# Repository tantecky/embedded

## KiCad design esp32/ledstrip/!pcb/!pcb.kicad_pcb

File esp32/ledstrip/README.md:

# LEDStrip

A board for controlling a WS2812B LED strip (5V). It contains ESP32 and a digital microphone INMP441.

## Content

- [PCB](!pcb/) design in KiCad
- [src/](src) an example app
- [3D printed enclosure](https://github.com/tantecky/embedded/tree/master/3Dprint/ledstrip) in FreeCAD

## Pics

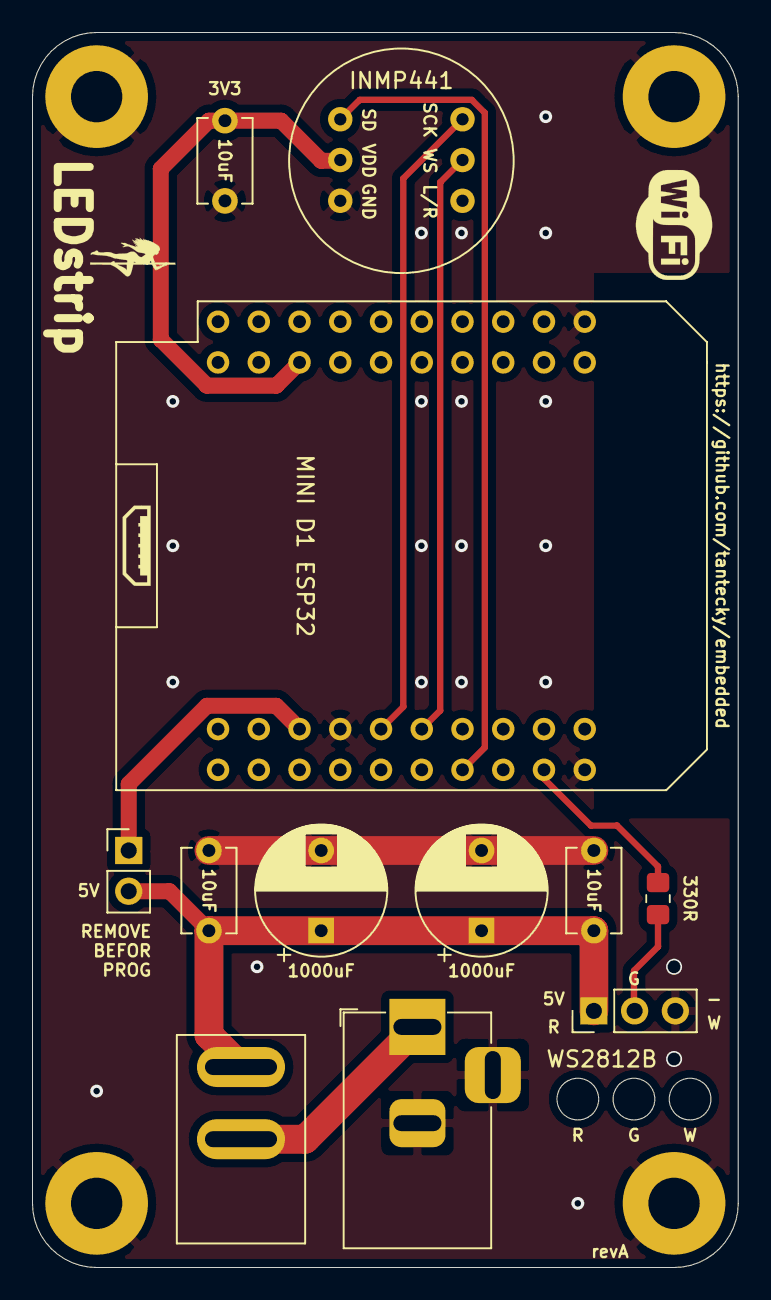
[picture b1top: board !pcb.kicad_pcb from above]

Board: 2 copper layers, 44.0 x 77.0 mm, 16 parts (0 on the bottom side), 10 nets.

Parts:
C1, C2: 1000u; CP_Radial_D8.0mm_P5.00mm
C3, C4, C5: 10u; C_Disc_D5.1mm_W3.2mm_P5.00mm
H1, H2, H3, H4: MountingHole_Pad; MountingHole_3.2mm_M3_Pad
J1: Barrel_Jack_Switch; BarrelJack_Horizontal
J2: Conn_01x03; PinHeader_1x03_P2.54mm_Vertical
JP1: Jumper_NC_Small; PinHeader_1x02_P2.54mm_Vertical
R1: 330R; R_0805_2012Metric_Pad1.20x1.40mm_HandSolder
SW1: SW_SPST; sw
U1: ESP32 MINI; ESP32_mini
U2: INMP441

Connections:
+3V3: C5.1, U1.16, U2.5
+5V: C1.1, C2.1, C3.1, C4.1, J2.1, JP1.2, SW1.2
GND: C1.2, C2.2, C3.2, C4.2, C5.2, H1.1, H2.1, H3.1, H4.1, J1.2, J1.3, J2.3, U1.1, U1.22, U1.33, U2.1, U2.4
unnamed: J1.1, SW1.1
unnamed: J2.2, R1.2
unnamed: JP1.1, U1.35
SCK: U1.31, U2.3
SD: U1.28, U2.6
STRIP: R1.1, U1.24
WS: U1.29, U2.2

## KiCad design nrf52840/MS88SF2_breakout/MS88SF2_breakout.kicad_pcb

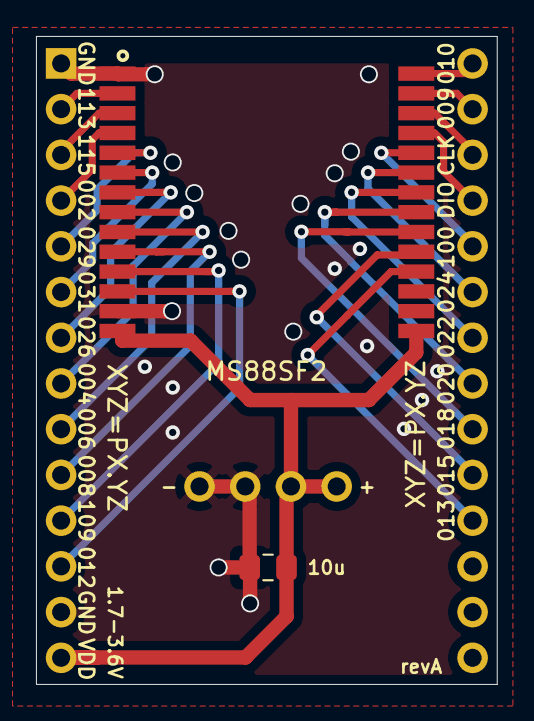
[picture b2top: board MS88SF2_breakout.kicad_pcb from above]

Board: 2 copper layers, 25.6 x 36.0 mm, 5 parts (0 on the bottom side), 24 nets.

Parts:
BT1: Battery_Cell; CR2032_holder
C1: 10uF; C_0805_2012Metric_Pad1.15x1.40mm_HandSolder
J1: Conn_01x14_Male; PinHeader_1x14_P2.54mm_Vertical
J2: Conn_01x14_Male; PinHeader_1x14_P2.54mm_Vertical_2row
U1: MS88SF2

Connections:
+3V3: BT1.1, C1.1, J1.14, U1.14, U1.15
GND: BT1.2, C1.2, J1.1, J1.13, U1.1, U1.13
P0.02: J1.4, U1.4
P0.04: J1.8, U1.8
P0.06: J1.9, U1.9
P0.08: J1.10, U1.10
P0.09: J2.27, U1.27
P0.10: J2.28, U1.28
P0.12: J1.12, U1.12
P0.13: J2.18, U1.18
P0.15: J2.19, U1.19
P0.18: J2.20, U1.20
P0.20: J2.21, U1.21
P0.22: J2.22, U1.22
P0.24: J2.23, U1.23
P0.26: J1.7, U1.7
P0.29: J1.5, U1.5
P0.31: J1.6, U1.6
P1.00: J2.24, U1.24
P1.09: J1.11, U1.11
P1.13: J1.2, U1.2
P1.15: J1.3, U1.3
SWCLK: J2.26, U1.26
SWDIO: J2.25, U1.25

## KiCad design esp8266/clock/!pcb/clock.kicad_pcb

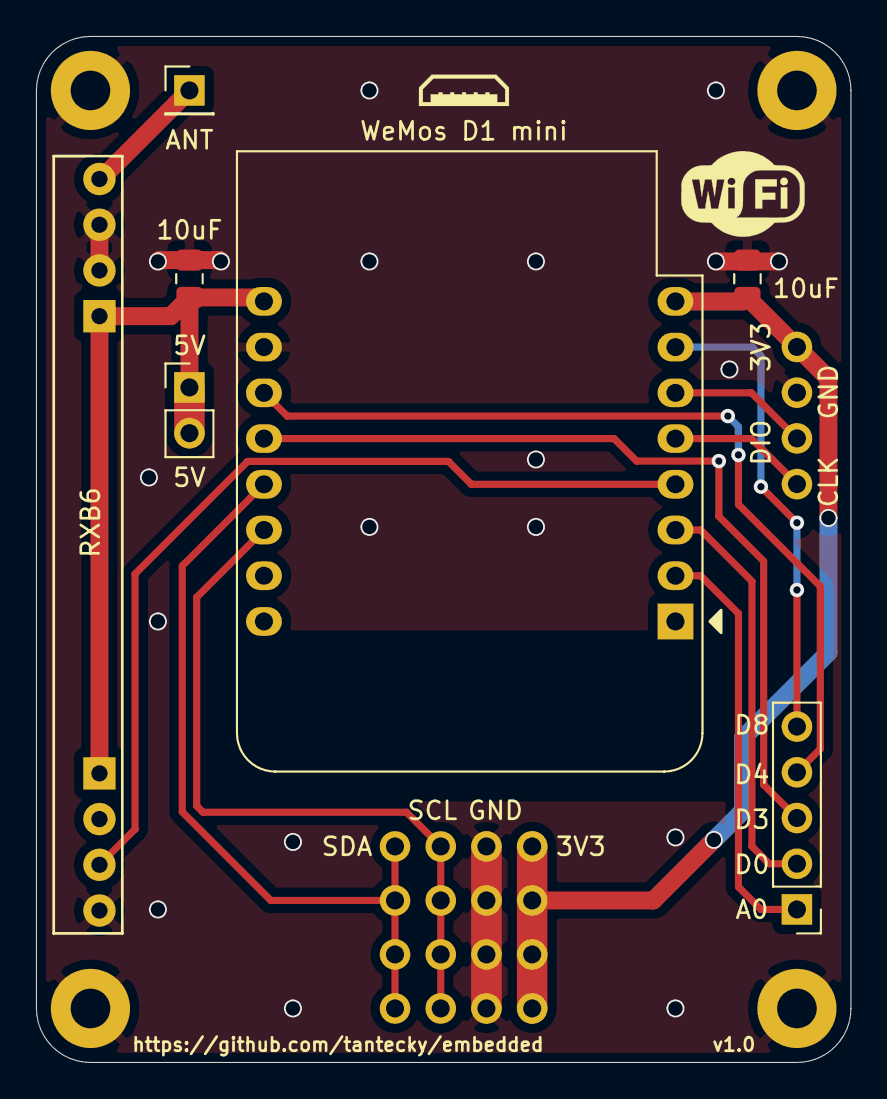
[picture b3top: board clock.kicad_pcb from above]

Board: 2 copper layers, 45.2 x 57.0 mm, 16 parts (0 on the bottom side), 14 nets.

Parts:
5V: Conn_01x01; PinHeader_1x02_P2.54mm_Vertical
10uF, 10uF#2: 10u; C_0805_2012Metric_Pad1.18x1.45mm_HandSolder
ANT: Conn_01x01; PinHeader_1x01_P2.54mm_Vertical
H1, H2, H3, H4: MountingHole_Pad; MountingHole_2.2mm_M2_Pad
J1: GPIO; PinHeader_1x05_P2.54mm_Vertical
RXB6: RXB6; rxb
U3: BME280; 4pinI2C
U4: OLED; 4pinI2C
U5: LED; 4pinTM1637
U6: SPARE; 4pinI2C
U7: SPARE2; 4pinI2C
WeMos D1 mini: WeMos_D1_mini; WEMOS_D1_mini_light

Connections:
+3V3: 10uF#2.2, U3.1, U4.1, U5.1, U6.1, U7.1, WeMos D1 mini.8
+5V: 5V.1, 5V.2, 10uF.1, RXB6.4, RXB6.5, WeMos D1 mini.9
A0: J1.1, WeMos D1 mini.2
ANT: ANT.1, RXB6.8
CLK: U5.4, WeMos D1 mini.5
D0: J1.2, WeMos D1 mini.3
D3: J1.3, WeMos D1 mini.12
D4: J1.4, WeMos D1 mini.11
D8: J1.5, WeMos D1 mini.7
DATA: RXB6.2, WeMos D1 mini.4
DIO: U5.3, WeMos D1 mini.6
GND: 10uF.2, 10uF#2.1, H1.1, H2.1, H3.1, H4.1, RXB6.1, RXB6.6, RXB6.7, U3.2, U4.2, U5.2, U6.2, U7.2, WeMos D1 mini.10
SCL: U3.3, U4.3, U6.3, U7.3, WeMos D1 mini.14
SDA: U3.4, U4.4, U6.4, U7.4, WeMos D1 mini.13

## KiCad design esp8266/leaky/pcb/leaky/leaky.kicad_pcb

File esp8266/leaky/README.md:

# Leaky - water detector
The repository contains a firmware example and KiCad files for open source hardware Leaky. For more info see
<a href="https://www.openhardware.io/view/8239/Leaky-water-detector" target="_blank">project's main page</a> and <a href="https://youtu.be/IXUa7aIcWfs" target="_blank">a short demo.</a>

## Firmware
For an example firmware see [main.cpp](src/main.cpp) and [config.hpp.example](src/config.hpp.example). When a leak is detected it starts beeping, connects to a WiFi and send a MQTT message to a given server.

To program the board an UART dongle is required (e.g. CP2102 USB 2.0 to UART). Is has to support 3V3, do not use 5V!
If you provide power through VBUS, remove batteries first.

To flash a program: 
1. Short jumper PROG
2. Connect UART (RXD->TX, TXD->RX)
3. Short jumper TURN_ON

## Home Assistant integration
Here is an example snippet for `automations.yaml` that forwards a received MQTT message and forwards it to Home Assistant mobile app:
```yaml
- id: 'Leaky'
  alias: Leak
  description: ''
  trigger:
  - platform: mqtt
    topic: leak/#
  condition: []
  action:
  - data_template:
      message: '{{ trigger.payload }}'
    service: notify.mobile_app_mi_a2_lite
  mode: single
  ```

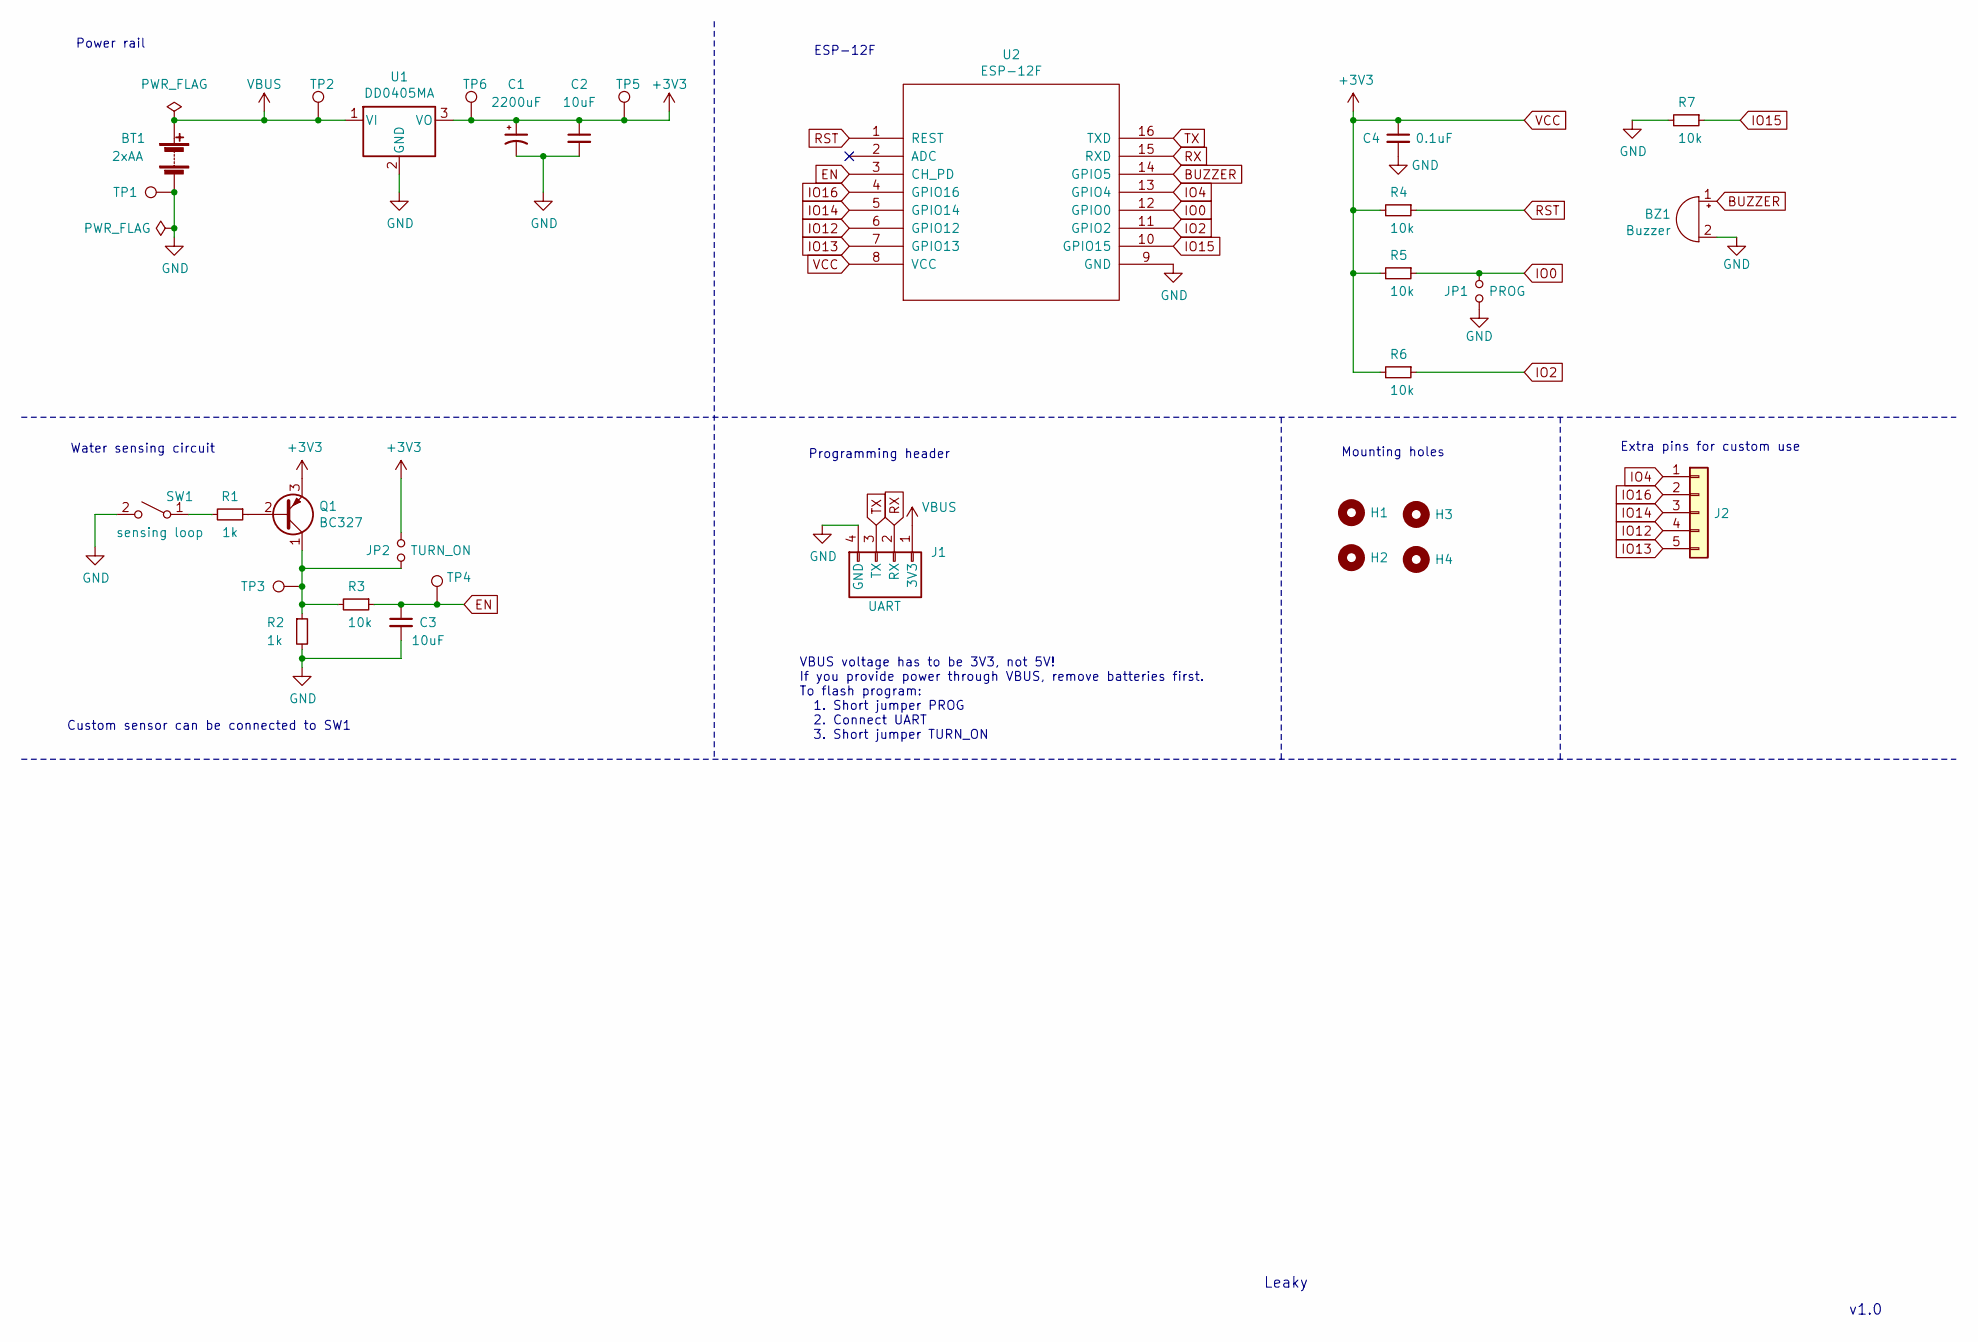
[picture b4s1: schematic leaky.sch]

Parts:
BT1: 2xAA; BatteryHolder_Keystone_2462_2xAA
BZ1: Buzzer; Buzzer_12x9.5RM7.6
C1: 2200uF; CP_Radial_D10.0mm_P5.00mm
C2, C3: 10uF; C_0805_2012Metric_Pad1.18x1.45mm_HandSolder
C4: 0.1uF; C_0805_2012Metric_Pad1.18x1.45mm_HandSolder
H1, H2, H3, H4: MountingHole; MountingHole_3.2mm_M3
J1: UART; PinHeader_1x04_P2.54mm_Vertical
J2: extra pins; PinHeader_1x05_P2.54mm_Vertical
JP1: PROG; PinHeader_1x02_P2.54mm_Vertical
JP2: TURN_ON; PinHeader_1x02_P2.54mm_Vertical
Q1: BC327; TO-92_Inline
R1, R2: 1k; R_0805_2012Metric_Pad1.15x1.40mm_HandSolder
R3, R4, R5, R6, R7: 10k; R_0805_2012Metric_Pad1.15x1.40mm_HandSolder
SW1: sensing loop; PinHeader_1x02_P2.54mm_Vertical
TP1, TP2, TP3, TP4, TP5, TP6: TestPoint; TestPoint_Pad_D1.0mm
U1: DD0405MA
U2: ESP-12F; ESP-12E_SMD

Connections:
BUZZER: BZ1.1 (-), U2.14 (GPIO5)
EN: C3.1, R3.1, TP4.1, U2.3 (CH_PD)
GND: BT1.2 (-), BZ1.2 (+), C1.2, C2.2, C3.2, C4.2, J1.4 (GND), JP1.2, R2.2, R7.2, SW1.2 (B), TP1.1, U1.2 (GND), U2.9 (GND)
IO0: JP1.1, R5.1, U2.12 (GPIO0)
IO2: R6.1, U2.11 (GPIO2)
IO4: J2.1, U2.13 (GPIO4)
IO12: J2.4, U2.6 (GPIO12)
IO13: J2.5, U2.7 (GPIO13)
IO14: J2.3, U2.5 (GPIO14)
IO15: R7.1, U2.10 (GPIO15)
IO16: J2.2, U2.4 (GPIO16)
unnamed: JP2.2, Q1.1 (C), R2.1, R3.2, TP3.1
unnamed: Q1.2 (B), R1.1
unnamed: R1.2, SW1.1 (A)
RST: R4.1, U2.1 (REST)
RX: J1.2 (RX), U2.15 (RXD)
TX: J1.3 (TX), U2.16 (TXD)
VBUS: BT1.1 (+), J1.1 (3V3), TP2.1, U1.1 (VI)
VCC: C1.1, C2.1, C4.1, JP2.1, Q1.3 (E), R4.2, R5.2, R6.2, TP5.1, TP6.1, U1.3 (VO), U2.8 (VCC)

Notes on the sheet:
Power rail
Water sensing circuit
Programming header
Extra pins for custom use
Mounting holes
VBUS voltage has to be 3V3, not 5V! If you provide power through VBUS, remove batteries first. To flash program: 1. Short jumper PROG 2. Connect UART 3. Short jumper TURN_ON
ESP-12F
Custom sensor can be connected to SW1
Leaky
v1.0

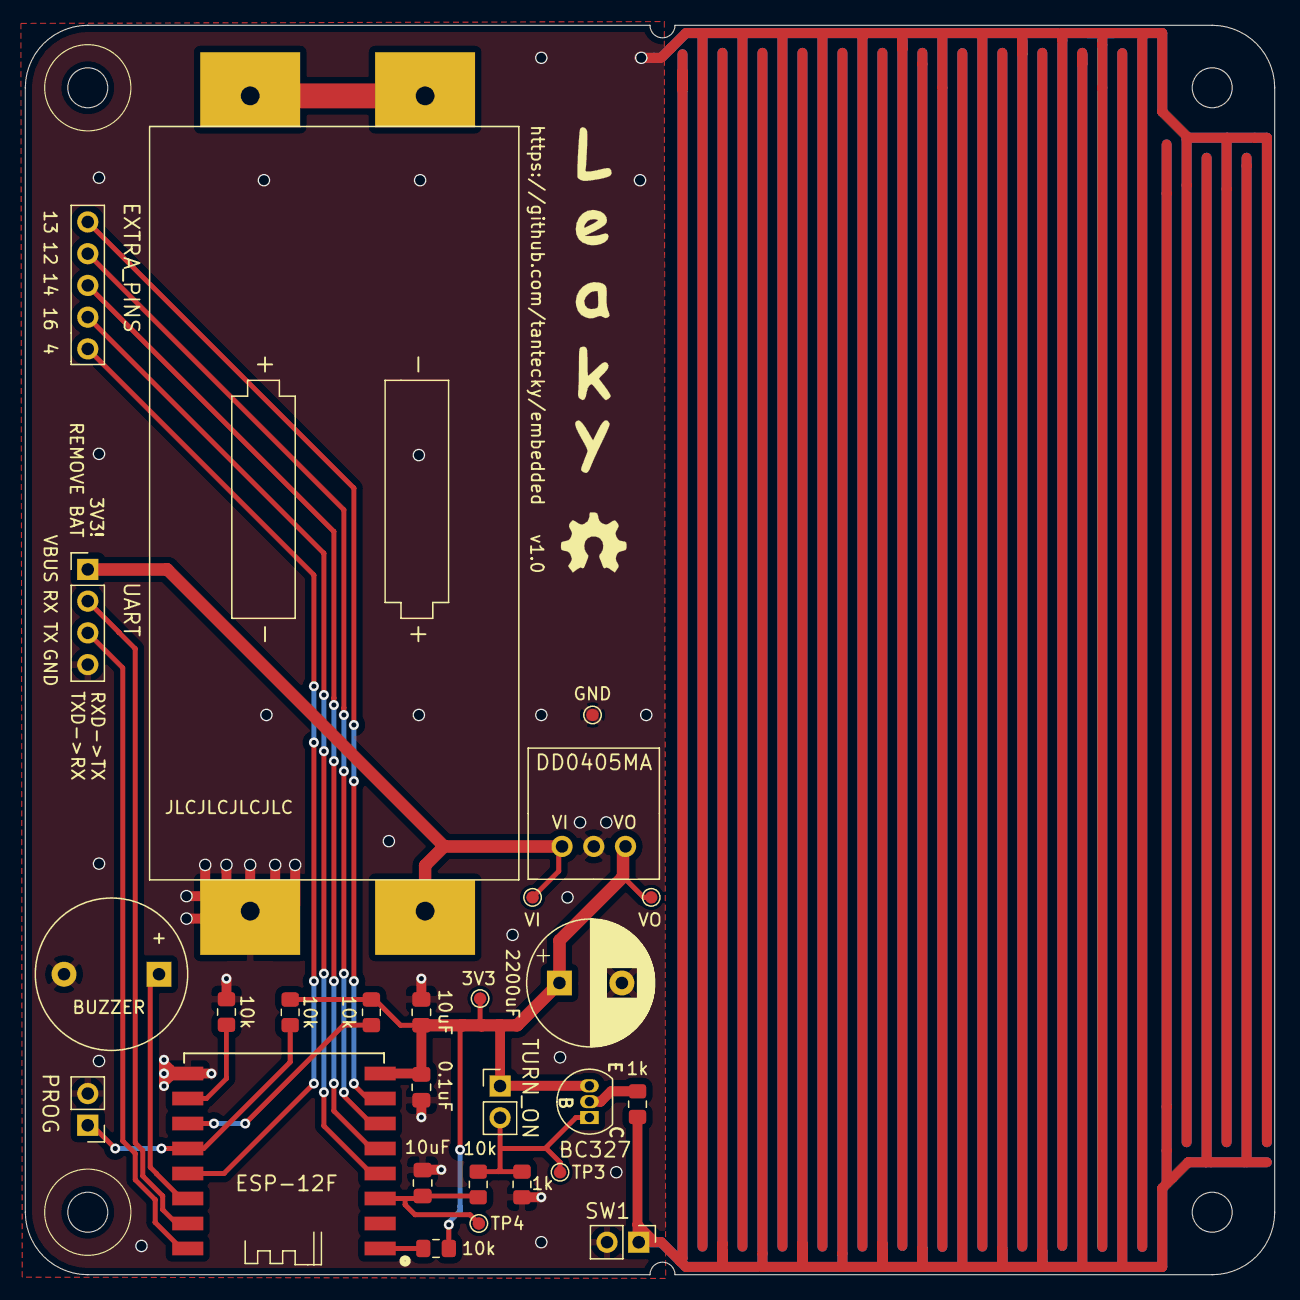
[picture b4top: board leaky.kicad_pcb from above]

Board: 2 copper layers, 100.0 x 100.0 mm, 31 parts (0 on the bottom side), 19 nets.

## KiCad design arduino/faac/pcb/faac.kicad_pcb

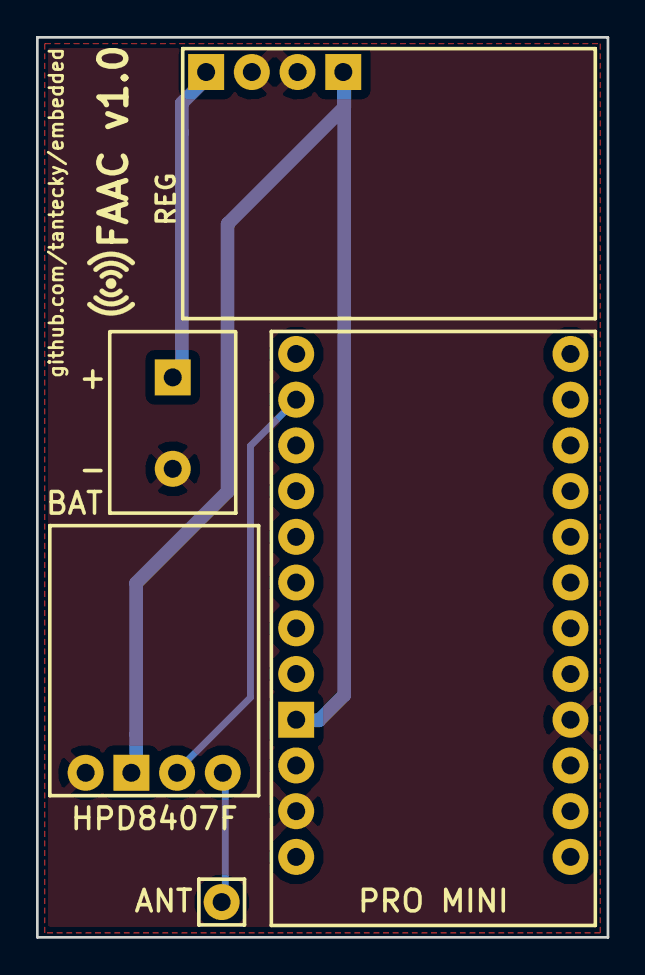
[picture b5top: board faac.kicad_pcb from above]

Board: 2 copper layers, 31.7 x 50.0 mm, 5 parts (0 on the bottom side), 5 nets.

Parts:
ANT: ANT; antenna
BAT: BatCon
HPD8407F: HPD8407-F
PRO MINI: ProMini
REG: Reg3V3

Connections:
GND: BAT.2, HPD8407F.1, PRO MINI.2, PRO MINI.16, REG.2, REG.3
unnamed: ANT.1, HPD8407F.4
unnamed: BAT.1, REG.4
unnamed: HPD8407F.2, PRO MINI.4, REG.1
unnamed: HPD8407F.3, PRO MINI.11

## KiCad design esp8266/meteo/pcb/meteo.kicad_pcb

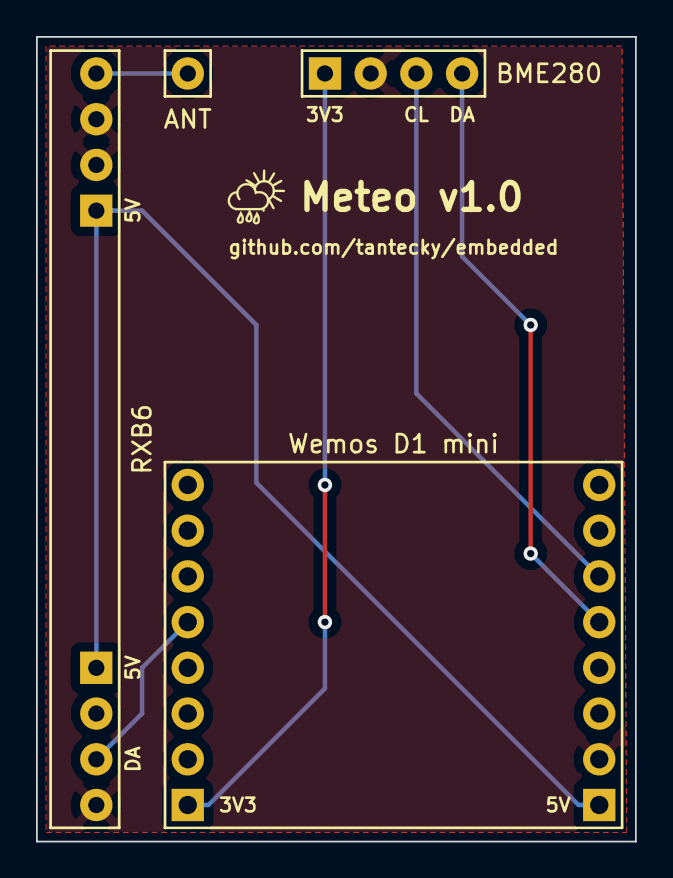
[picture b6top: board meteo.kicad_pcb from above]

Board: 2 copper layers, 33.3 x 44.7 mm, 4 parts (0 on the bottom side), 7 nets.

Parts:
ANT: Antenna; antenna
BME280: bme280pbc; bme280pcb
RXB6: rxb
Wemos D1 mini: WeMos_mini; d1

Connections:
GND: BME280.2, RXB6.1, RXB6.6, RXB6.7, Wemos D1 mini.2
unnamed: ANT.1, RXB6.8
unnamed: RXB6.4, RXB6.5, Wemos D1 mini.1
unnamed: BME280.4, Wemos D1 mini.5
unnamed: BME280.3, Wemos D1 mini.6
unnamed: RXB6.2, Wemos D1 mini.12
unnamed: BME280.1, Wemos D1 mini.16

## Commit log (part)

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2015-12-31 netalarm: Add more tests
2015-12-31 netalarm: Fix bug in PacketReader
2015-12-31 netalarm: Remove traling spaces
2016-01-01 netalarm: Add possibility to set DNS, gateway
2016-01-02 netalarm: Add option to disable remote control
2016-01-03 netalarm: Add option to specify state on power on
2016-01-29 Receive433: Add sample code
2016-02-01 netalarm: Enable packing library without building
2016-02-24 NetAlarm: modify default settings
2016-03-09 netlarm: Fix remote control freezing
2016-10-30 ReedSwitch: Initial release
2016-10-30 ReedSwitch: Improve overflow handling
2016-11-13 ReedSwitch: Modify for Arduino Nano
2016-11-20 dalarm: Load config from JSON instead
2016-11-20 dalarm: Test MQTT subscribe
2016-12-31 dalarm: Implement reconnection logic
2017-01-22 dalarm: Add pin layout
2017-03-15 dalarm: Adjust for home assistant
2017-04-01 dalarm: Implement debouncing
2017-10-15 dalarm: Move to a project dir
2017-10-15 falarm: Init a project
2017-10-21 falarm: Make it production ready
2017-12-10 arduino: Move to a seperate folder
2017-12-24 CrestaTest: Add a project
2017-12-26 faac: Add a project
2018-03-19 ReedSwitch: Increase delay
2018-05-08 falarm: Disable WiFi to make it more relaible
2018-05-19 falarm_ard: Initial commit
2018-05-26 falarm_ard: Switch to a production conf
2018-09-02 meteo: Initial commit
2018-09-02 meteo: Change db password
2018-09-04 meteo: Use static IP
2018-09-08 meteo: Start working on PCB
2018-09-09 meteo: Add tracks
2018-09-09 meteo: Add a logo
2018-09-10 meteo: Send v1.0 to Allpcb fab
2018-09-16 meteo: Small tweaks
2018-12-27 faac: Init PCB
2018-12-27 faac: Start routing
2018-12-28 faac: Add more routes
2018-12-28 faac: Increase spacing
2018-12-28 faac: Add cuts
2018-12-29 faac: Add labels
2018-12-29 faac: Add a logo
2019-01-25 faac: Reduce send delay
2020-03-12 faac: Add box for 3D print
2020-03-22 stm32: LED blinking
2020-06-15 rcontrol: Add project
2020-06-17 3Dprint: Add shade design
2020-06-21 pwm: PWM beep for attiny85
2020-07-04 pwm: Use better ISR
2020-07-08 3Dprint: Add fan stand
2020-07-10 pwm: Tune comments
2020-07-13 pwm: Add watch dog
2020-07-15 pwd: Adjust sleep period
2020-07-15 pt2272: Init a sketch
2020-07-28 rcontrol: Add basic auth
2020-07-28 3Dprint: Add esp pool box
2020-07-31 esp32: Add info script
2020-07-31 3Dprint: Pool printed
2020-08-07 3Dprint: Add relay box
2020-08-12 3dprint: Print box
2020-09-30 leaky: Init repo
2020-10-01 leaky: Switch to task scheduler
2020-10-03 leaky: Init pcb design
2020-10-04 leaky: Add ESP8266
2020-10-15 leaky: Add workspace
2020-10-18 leaky: Adjust schematic
2020-10-21 Assign more footprints
2020-10-24 stm32: Add PIO project for F4
2020-10-24 stm32: Move libs
2020-10-24 stm32: Move freertos
2020-10-24 stm32: Test usb serial
2020-10-26 leaky" Adjust footprint
2020-10-26 leaky: Fix courtyard
2020-10-28 stm32: Add main.cpp
2020-10-28 stm32: rtos is working
2020-10-28 stm32: Fix USB
2020-10-28 stm32: Add USB echo
2020-10-29 stm32: Start implementing printf
2020-10-29 stm32: printf working
2020-10-29 stm32: Add INA219
2020-10-30 stm32: Voltage reading has wrong values
2020-10-30 stm32: Adjust clocks
2020-10-30 stm32: Switch to CubeIDE
2020-10-30 stm32: Voltage reading is now working
2020-10-31 stm32: Add C++ class for INA219
2020-10-31 stm32: Fix USB IRQ priority for RTOS
2020-10-31 stm32: Add PWM
2020-11-01 stm32: Adjust .gitignore
2020-11-01 stm32: Switch to CRLF
2020-11-01 stm32: Add dac
2020-11-02 stm32: Adjust printing
2020-11-03 stm32: Remove PWM
2020-11-03 stm32: Add pressure sensor
2020-11-04 stm32: Add PID
2020-11-05 stm32: Change baudrate
2020-11-05 stm32: Add DAC class
2020-11-05 stm32: Start working on PID
2020-11-05 Fix crashes
2020-11-05 stm32: Printf float is causing lock
2020-11-05 stm32: Fix USB hang ups
2020-11-07 leaky: Add description
2020-11-07 leaky: Start position components
2020-11-07 leaky: More reposition
2020-11-07 leaky: More repos
2020-11-08 leaky: Test routing
2020-11-09 stm32: Fix USB printf
2020-11-09 stm32: Add wind up check
2020-11-09 stm32: Add RNG
2020-11-15 leaky: Start working on bat footprint
2020-11-15 leaky: Add bat footprint
2020-11-15 leaky: Adjust cap
2020-11-16 leaky: Update schema
2020-11-16 leaky: Position test points
2020-11-16 leaky: Adjust PCB
2020-11-17 leaky: Adjust RX TX
2020-11-17 leaky: Start routing
2020-11-20 stm32: Removed
2020-11-20 leaky: Adjust bat 3d model
2020-11-20 leaky: Move TP4
2020-11-20 leaky: Add sense loop to top
2020-11-20 leaky: Add more traces
2020-11-20 leaky: Remove solder mask
2020-11-20 leaky: Try upload gerbs
2020-11-21 leaky: Adjust bot layer
2020-11-21 leaky: Add bot sensing
2020-11-21 leaky: Add logo
2020-11-21 leaky: Add stiching vias
2020-11-21 leaky: Small tweaks
2020-11-22 leaky: Send v1.0 to jlcpcb
2020-12-10 leaky: Add profile for ESP-12F
2020-12-10 leaky: Add schematic
2020-12-10 leaky: Move dirs
2020-12-11 leaky: Add pics
2020-12-11 leaky: Improve doc
2020-12-12 leaky: Add automations snippet
2020-12-12 leaky: update readme
2020-12-17 clock: Init
2020-12-17 clock: Switch to TaskScheduler
2020-12-17 clock: Add BME
2020-12-19 clock: Debug resets
2020-12-19 clock: Fix crash
2020-12-20 clock: Lower contrast during night
2020-12-24 bme680: Add BME680 test project
2020-12-25 clock: Show pressure
2020-12-26 clock: Log to Influx
2020-12-26 clock: Start logger
2020-12-28 clock: Switch to 30 min interval
2021-01-03 dongle: Add fin
2021-01-05 dongle: First print
2021-01-05 dongle: Print version 2
2021-01-05 dongle: Print 3
2021-01-11 meteo: Start adding BME680
2021-01-11 meteo: Add BME680
2021-01-12 meteo: Switch to production
2021-01-16 Add TM1637 test code
2021-01-17 clock: Small fixes
2021-01-17 clock: Add LED display
2021-01-17 clock: Sync time every 15 seconds
2021-01-18 clock: Adjust println
2021-01-30 clock: Add more syms
2021-01-31 clock: Start routing
2021-02-02 clock: Prepare routing
2021-02-02 clock: Rough roouting done
2021-02-02 clock: Add dimensions
2021-02-02 clock: Almost ready
2021-02-02 clock: Send v10 to fab
2021-02-14 nrf5: init
2021-02-14 nrf5: Firmware is working
2021-02-15 nrf: Add BLE blinky
2021-02-20 nrf5: Add missing vscode
2021-02-26 nrf5: Add includes
2021-02-26 nrf5: Add ble_app_hrs
2021-02-28 nrf5: Add LEDs
2021-02-28 nrf5: Remove hts
2021-03-01 nrf5: Fix missing bat
2021-03-02 nrf5: Enable RTT
2021-03-03 nrf5: Adjust build scripts
2021-03-03 nrf5: Add custom service
2021-03-04 nrf5: Switch to jlink
2021-03-06 nrf5: Fix stack overflow
2021-03-06 nrf5: Improve printk
2021-03-06 nrf5: Add bt init code
2021-03-07 nrf5: It compiles
2021-03-07 nrf5: Blink is working
2021-03-07 nrf5: Init MAX
2021-03-07 nrf5: Temp measurement is working
2021-03-08 nrf5: Fix cpp config
2021-03-10 nrf5: Send temp over BLE
2021-03-11 3Dprint: Add M2 nut pocket
2021-03-11 nrf5: Temp over BLE is correct
2021-03-11 nrf5: Enable blue LED
2021-03-12 3Dprint: Init clock box
2021-03-12 3Dprint: Add LED pocket
2021-03-12 3Dprint: Add OLED
2021-03-12 3Dprint: Add a ledge
2021-03-12 3Dprint: Finish OLED
2021-03-13 3Dprint: Add USB pocket
2021-03-14 nrf5: Add MS88SF2 breakout board
2021-03-14 nrf5: Start routing
2021-03-14 nrf5: Prepare for routing
2021-03-15 3Dprint: Increase nut size
2021-03-15 3Dprint: Reduce pocket OLED offset
2021-03-15 3Dprint: Make USB pocket larger
2021-03-15 nrf5: Adjust position
2021-03-15 3Dprint: Fix screw hole
2021-03-16 3Dprint: Test wifi logo
2021-03-16 3Dprint: Clock 1st print
2021-03-16 clock: Print current temp to console for debugging
2021-03-16 3Dprint: Add used logos
2021-03-17 nrf5: Add edge cuts
2021-03-17 nrf5: Add dims
2021-03-17 3Dprint: Add a lid
2021-03-17 3Dprint: Add wedge to a lid
2021-03-17 nrf5: Improve grounding
2021-03-17 3Dprint: Adjust lid lip
2021-03-18 clock: Adjust brightness
2021-03-18 clock: Add fail refresh interval
2021-03-19 nrf5: Add 10u cap
2021-03-20 nrf5: Adjust silk screen
2021-03-20 nrf5: Add panelize script
2021-03-20 nrf5: Edit foot for panelize
2021-03-21 ledstrip: Init a project
2021-04-12 nrf5: Add bat holder
2021-04-22 clock: Obey light saving
2021-04-24 clock: Fix leading zero
2021-04-30 ledstrip: Add test code
2021-05-01 ledstrip: Adjust pins
2021-05-01 ledstrip: Recording is working
2021-05-02 ledstrip: Add custom recorder
2021-05-02 ledstrip: Switch to float
2021-05-03 ledstrip: Adjust plotting
2021-05-03 ledstrip: Disable wifi sending
2021-05-03 ledstrip: Add dft
2021-05-03 ledstrip: Add FFT test case
2021-05-04 ledstrip: Add FftFun
2021-05-04 ledstrip: Add more data
2021-05-04 ledstrip: Add const modifier
2021-05-04 ledstrip: Add Table for sin/cos lookup
2021-05-04 ledstrip: Table sin/cos cache is working
2021-05-05 ledstrip: Compute FFT
2021-05-05 ledstrip: Add mag**2 calculation
2021-05-05 ledstrip: Add mag calculation
2021-05-05 ledstrip: Calculate magnitude
2021-05-06 ledstrip: Clean up code
2021-05-06 ledstrip: Detect max freq in real time
2021-05-06 ledstrip: Print bands
2021-05-07 ledstrip: Assign values to bands
2021-05-07 ledstrip: Add Hann window
2021-05-07 ledstrip: Add window func
2021-05-08 ledstrip: Add LED controller
2021-05-08 ledstrip: Add pallette
2021-05-09 ledstrip: Adjust bands
2021-05-10 ledstrip: Fix LED indexing
2021-05-17 ledstrip: Adjust refresh interval
2021-05-19 3Dprint: Add jack extractor
2021-06-20 ledstrip: Improve schema
2021-06-25 ledstrip: Add basic schematic
2021-06-25 3Dprint: Add hook
2021-06-26 3Dprint: Hook is finished
2021-06-26 Add a switch
2021-06-26 ledstrip: Add SW
2021-07-02 ledstrip: Adjust switch position
2021-07-07 ledstrip: Start routing
2021-07-08 ledstrip: Routing is almost done
2021-07-08 ledstrip: Ready for fab
2021-07-10 ledstrip: Reorient power switch
2021-07-10 ledstrip: Adjust labels
2021-07-10 nrf5: Add panel
2021-07-10 ledstrip: Add logo
2021-07-11 nrf5: Send to a fab
2021-09-07 3Dprint: start working on ledstrip box
2021-09-07 3Dprint: add side walls
2021-09-09 3Dprint: add corner
2021-09-09 3Dprint: Add more corners
2021-09-09 3Dprint: add M3nut
2021-09-10 3Dprint: add nut pockets
2021-09-10 3Dprint: add USB cutout
2021-09-11 3Dprint: pre-slice
2021-09-11 3Dprint: add lid lip
2021-09-11 3Dprint: update TechDraw
2021-09-13 3Dprint: print 1st LEDstrip box version
2021-09-13 3Dprint: print a lid
2021-09-14 3Dprint: add side lid wall
2021-09-17 ledstrip: Add moving averaging
2021-09-17 ledstrip: average led color
2021-09-20 3Dprint: Init tuner project
2021-09-21 3Dprint: Add stands
2021-09-21 3Dprint: Walls added
2021-09-21 3Dprint: Add coax cut
2021-09-29 3Dprint: Bottom first print try
2021-09-30 3Dprint: Increase spike dia
2021-09-30 3Dprint: Second print attempt for bottom
2021-09-30 3Dprint: Widen spikes
2021-10-02 3Dprint: Add lid for testing
2021-10-09 3Dprint: Start working on lid
2021-10-11 3Dprint: Reduce lid inner wall
2021-10-11 3Dprint: Losen inner walls even more
2021-10-11 3Dprint: Fins added
2021-10-15 spice: Add my models
2021-11-15 nrf5: Switch to VS Code
2021-11-15 nrf5: Reformat source
2021-11-15 nrf5: Add a macro for dev board detection
2021-11-15 nrf5: Do not hardcode SPI pins
2021-11-15 nrf5: Add MS88SF2 board
2021-11-15 nrf5: Change pins for non-dev board
2021-11-17 nrf5: Start working on simple Android app
2021-11-17 nrf5: Scanning is working
2021-11-17 nrf5: Fix root location
2021-11-18 nrf5: Connect to a GATT device
2021-11-18 nrf5: Remove depracated method
2021-11-18 nrf5: Switch to startScan
2021-11-18 nrf5: Use extension methods instead
2021-11-18 nrf5: Read temperature
2021-11-18 nrf5: Start refactoring code
2021-11-19 nrf5: Android app is done
2021-11-19 nrf5: Add a screenshot
2021-11-19 nrf5: Add RSSI info
2021-11-19 nrf5: Keep screen on
2021-11-24 nrf5: Fix for devices with null name
2021-11-24 nrf5: Fix paths
2021-11-29 ledstrip: Add README.md
2022-03-01 3Dprint: Add Meetup logo
2022-04-23 3Dprint: Add funnel
2022-05-18 3Dprint: First SoapSpike version
2022-09-27 3Dprint: Add SlowStart box
2022-09-27 3Dprint: Add a lid for soft start
2022-10-31 3Dprint: Increase hole
2022-10-31 3Dprint: Surf increase length to 50 mm
2022-11-01 3Dprint: Adjust slicer settings
2022-11-01 3Dprint: Surf lower temperature
2022-11-01 3Dprint: Set surf length to 60 mm
2023-05-18 3Dprint: Add oval
2023-06-12 3Dprint: Add a cup
2023-06-26 3Dprint: Wedge for my fridge
2023-06-27 3Dprint: Make the wedge bigger
2023-06-28 3Dprint: Add quad as well
2023-10-21 wedge: Add quad bathroom
